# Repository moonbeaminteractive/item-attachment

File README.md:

# item-attachment
attachments for additional features including weapon features

# Parts List </br>
3d printed parts</br>
Various Resisters (2 per Pickup)</br>
Soldering Tabs for connections</br>

# How they Work </br>

The Pickups are basically a voltage regulator circuit made of 2 resistors.  The resistors form an upside down V where the bottom two connections are the power and ground and the top (where the resistors meet) is the reduced voltage output.</br>

The output voltages below 1.0 volts are traps which can cause harm to the player who tries to use them or somehow incacitates the player.</br>

The output voltages between 1.0 and 2.0 volts are beneficial to the players health in that they will shield or give them faster healing abilities.</br>

The output voltages above 2.0 volts are offensive buffs which increase a weapons ability to do damage or give it faster recharge times.</br>

# Voltage Divider Resistors
See this document for our analysis of resistor dividers:
https://github.com/moonbeaminteractive/item-attachment/blob/master/references/voltageDividerCalculations.xlsx

&nbsp;&nbsp; VCC <br>
&nbsp;&nbsp;&nbsp;&nbsp;&nbsp; |<br>
&nbsp; < R1 ><br>
&nbsp;&nbsp;&nbsp;&nbsp;&nbsp; |<br>
&nbsp;&nbsp;&nbsp;&nbsp; +--------< R3 >------ to Analog pin on MCU<br>
&nbsp;&nbsp;&nbsp;&nbsp;&nbsp; |<br>
&nbsp; < R2 ><br>
&nbsp;&nbsp;&nbsp;&nbsp;&nbsp; |<br>
&nbsp;&nbsp; GND<br>

ASCII based voltage divider circuit diagram

Since these resistor dividers are connected to VCC, they will always be draining power from VCC. We add an additional resistor, R3, to control the lowest impedance values. We want to make them as small as possible. We can go as small as 100MOhm of total impedance. If we expect to sample different analog values rapidly, then we should keep the total impedance less than 10K. However, for our resistor dividers, we expect the analog voltage value to be constant, so designing a very high impedance circuit design is the best solution. R3 could be 10K, but 100K uses even less current. Even 1MOhm or 10MOhm resistor values for R3 would work too, but resistors over 1MOhm start to become more expensive, while 10K and 100K are commonly available.

Table of resistor values

| ID | R1 | R2 | R3 | 10-bit |
| --- | --- | --- | --- | --- |
| 0 | 100k | 100 | 100k | 1 |
| 4 | 82k | 15k | 100k | 158 |
| 8 | 68k | 33k | 100k | 335 |
| 12 | 47k | 47k | 100k | 512 |
| 16 | 33k | 68 | 100k | 689 |
| 20 | 15k | 82k | 100k | 866 |
| 24 | 100 | 100k | 100k | 1023 |

We used this tool:
http://www.electronics2000.co.uk/calc/potential-divider-calculator.php

To compute resistor values using E12 resistor to have a total resistance of around 100K ohms. Assuming only a 5% accuracy in resistors (we use 1% accurate resistors) as worst case scenario, we are able to easily differentiate 25 distint values. We begin by using the first set

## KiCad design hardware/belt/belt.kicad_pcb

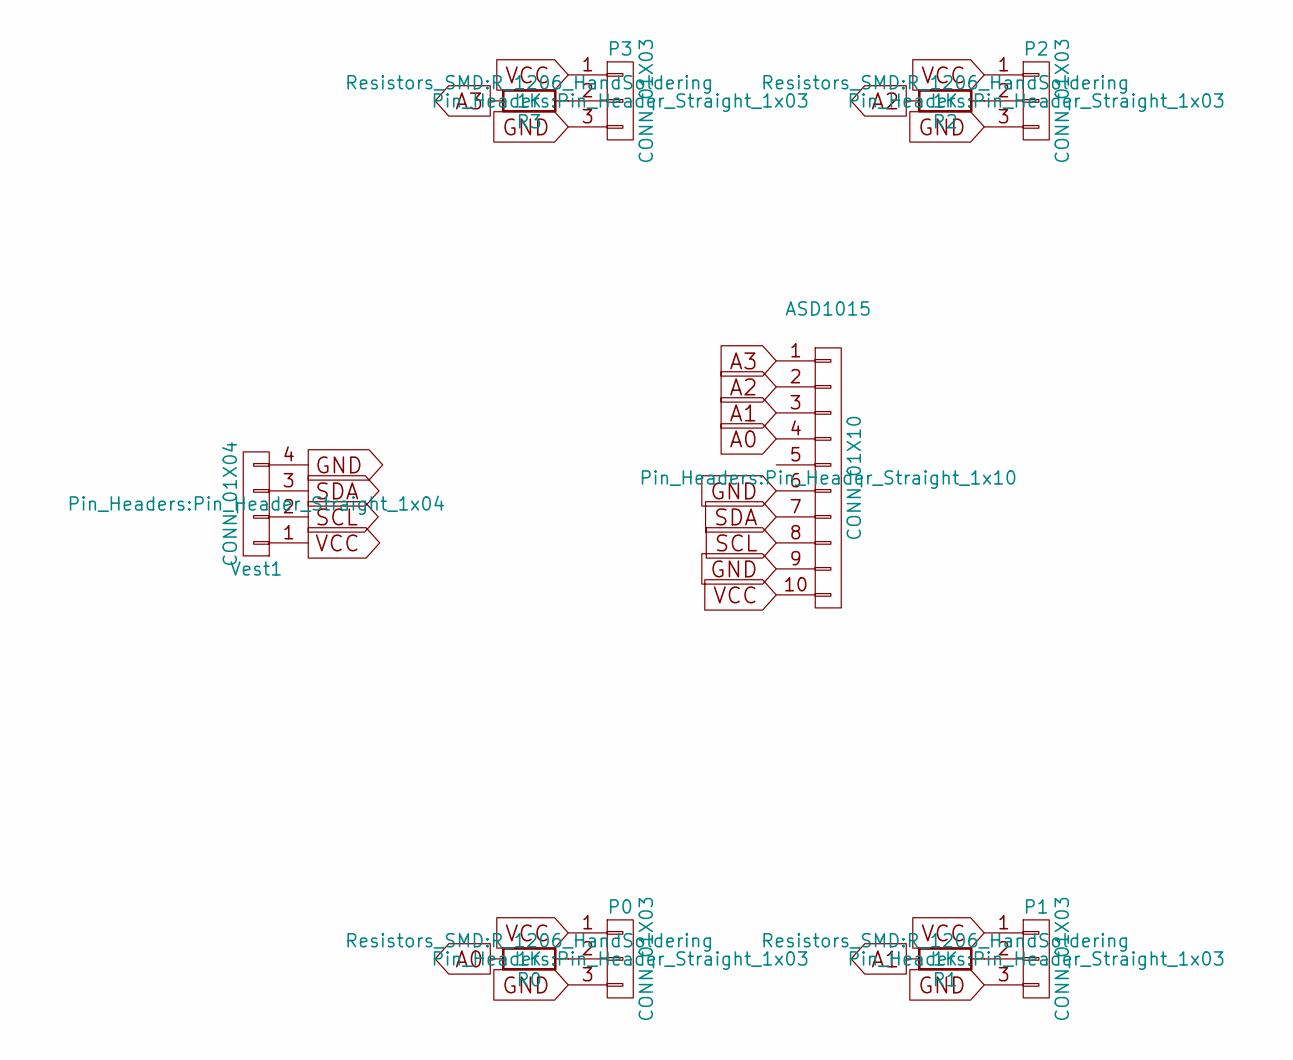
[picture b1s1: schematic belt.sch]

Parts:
ASD1015: CONN_01X10; Pin_Header_Straight_1x10
P0, P1, P2, P3: CONN_01X03; Pin_Header_Straight_1x03
R0, R1, R2, R3: 1K; R_1206_HandSoldering
Vest1: CONN_01X04; Pin_Header_Straight_1x04

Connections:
A0: ASD1015.4, R0.2
A1: ASD1015.3, R1.2
A2: ASD1015.2, R2.2
A3: ASD1015.1, R3.2
GND: ASD1015.6, ASD1015.9, P0.3, P1.3, P2.3, P3.3, Vest1.4
unnamed: P0.2, R0.1
unnamed: P1.2, R1.1
unnamed: P2.2, R2.1
unnamed: P3.2, R3.1
SCL: ASD1015.8, Vest1.2
SDA: ASD1015.7, Vest1.3
VCC: ASD1015.10, P0.1, P1.1, P2.1, P3.1, Vest1.1

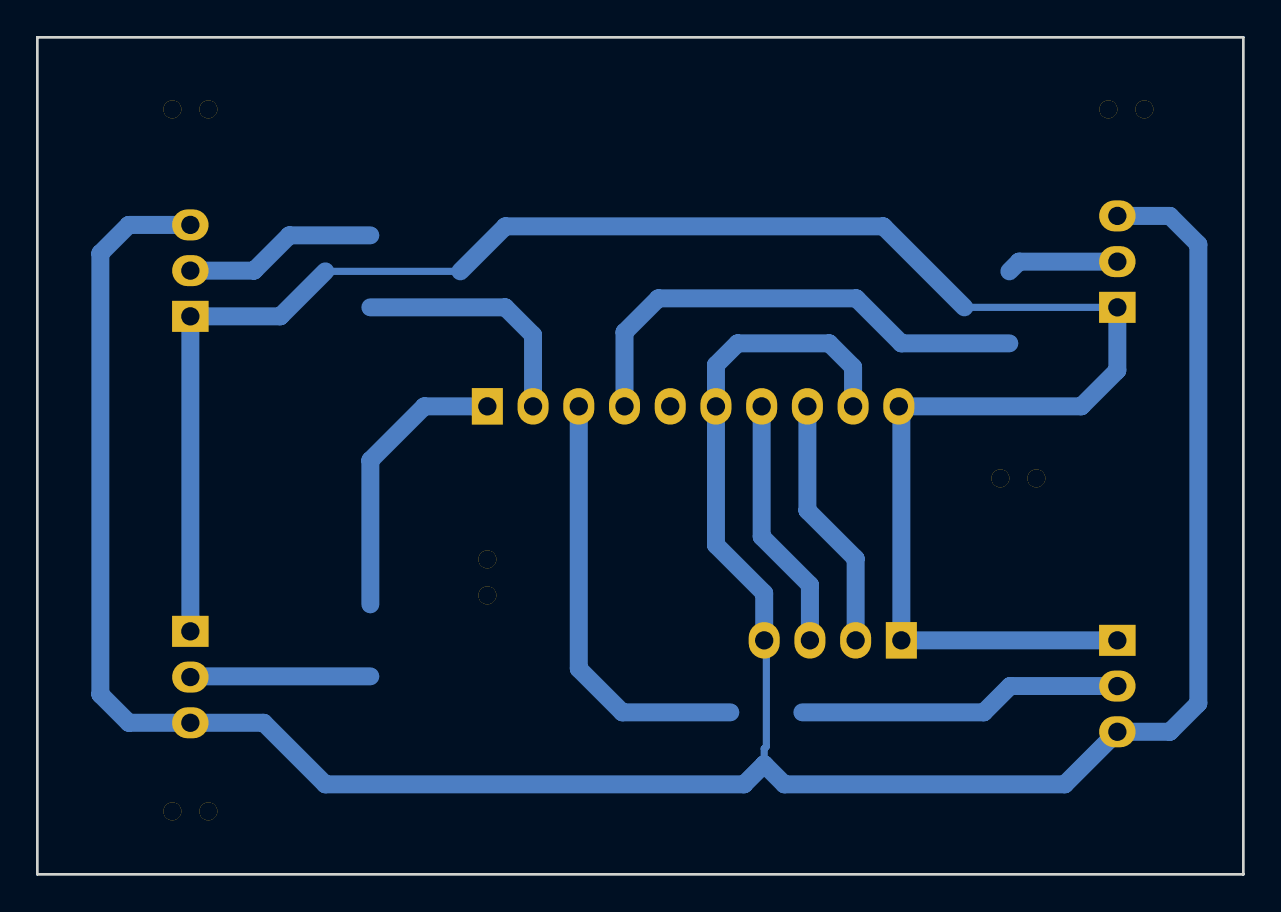
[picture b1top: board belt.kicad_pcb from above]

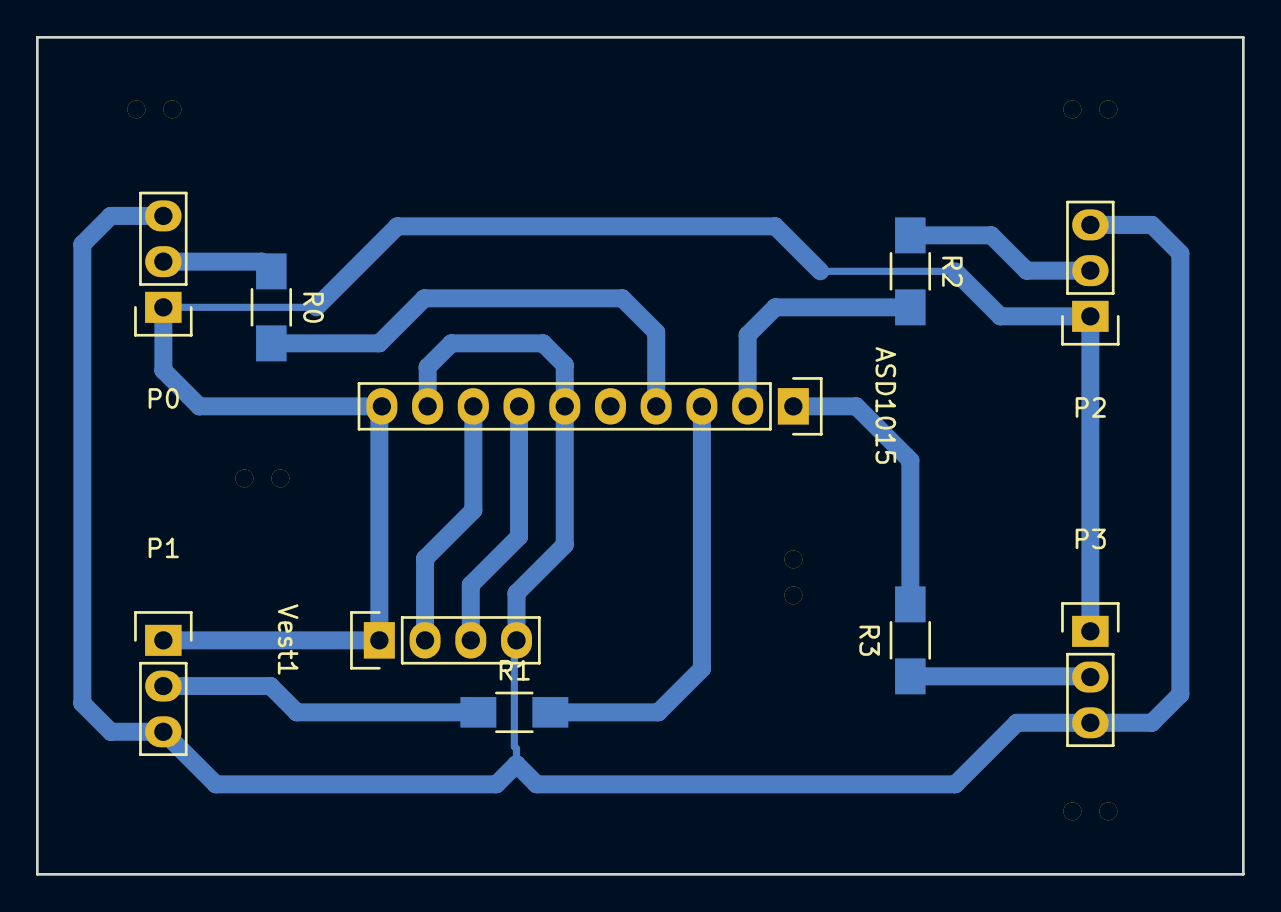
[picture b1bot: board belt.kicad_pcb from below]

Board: 2 copper layers, 67.0 x 46.5 mm, 10 parts (10 on the bottom side), 12 nets.

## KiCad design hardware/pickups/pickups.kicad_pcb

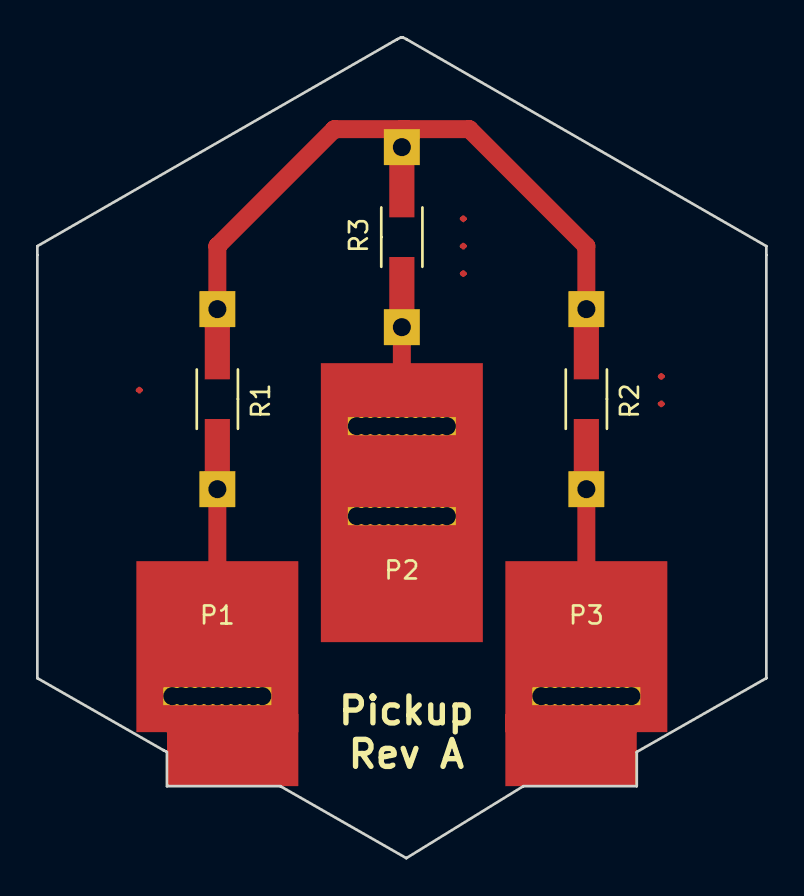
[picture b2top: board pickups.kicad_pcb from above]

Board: 2 copper layers, 40.5 x 45.6 mm, 6 parts (0 on the bottom side), 4 nets.

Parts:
P1: VCC; pickup_contact_bottom_left
P2: OUT; pickup_contact
P3: GND; pickup_contact_bottom_right
R1, R2, R3: R; Resistor_SMD+THTuniversal_1206_RM10_HandSoldering

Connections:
unnamed: P1.1, R1.2
unnamed: P2.1, R3.1
unnamed: P3.1, R2.2
unnamed: R1.1, R2.1, R3.2

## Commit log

2016-11-13 added folders
2016-11-13 created example 2 pad connector with single resistor
2016-11-14 added resistor divider spreadsheet
2016-11-20 Create design
2016-11-20 Create icons
2016-11-21 Added Models to models folder
    Maya files
    Printer files
    Gcode and STL
2016-11-21 Added a diagram to the readme
    Added parts list
    diagram
    and description of how they will work
2016-11-22 Create thing
2016-11-28 updated voltage divider calculations
2016-11-29 modified sleeves and pickup models and arduino sketch
    added extra slots for solder tabs on 3d parts
    created a sketch to work with the mcp3008 and the pickups attached to an
    arduino mini pro 3.3 volts 8mhz
2016-12-03 Adding pickups board design
2016-12-03 Upload SVG export for pickups edges and front
2016-12-11 Update pickups pcb
2016-12-12 Fix R ID 20 order
2016-12-13 changed resistor footprints to universal type
2016-12-14 Create pickups
2016-12-15 Adding pickups belt hardware and software
2016-12-18 Remove .DS_Store files
2016-12-18 Adding reading value for NUKE
